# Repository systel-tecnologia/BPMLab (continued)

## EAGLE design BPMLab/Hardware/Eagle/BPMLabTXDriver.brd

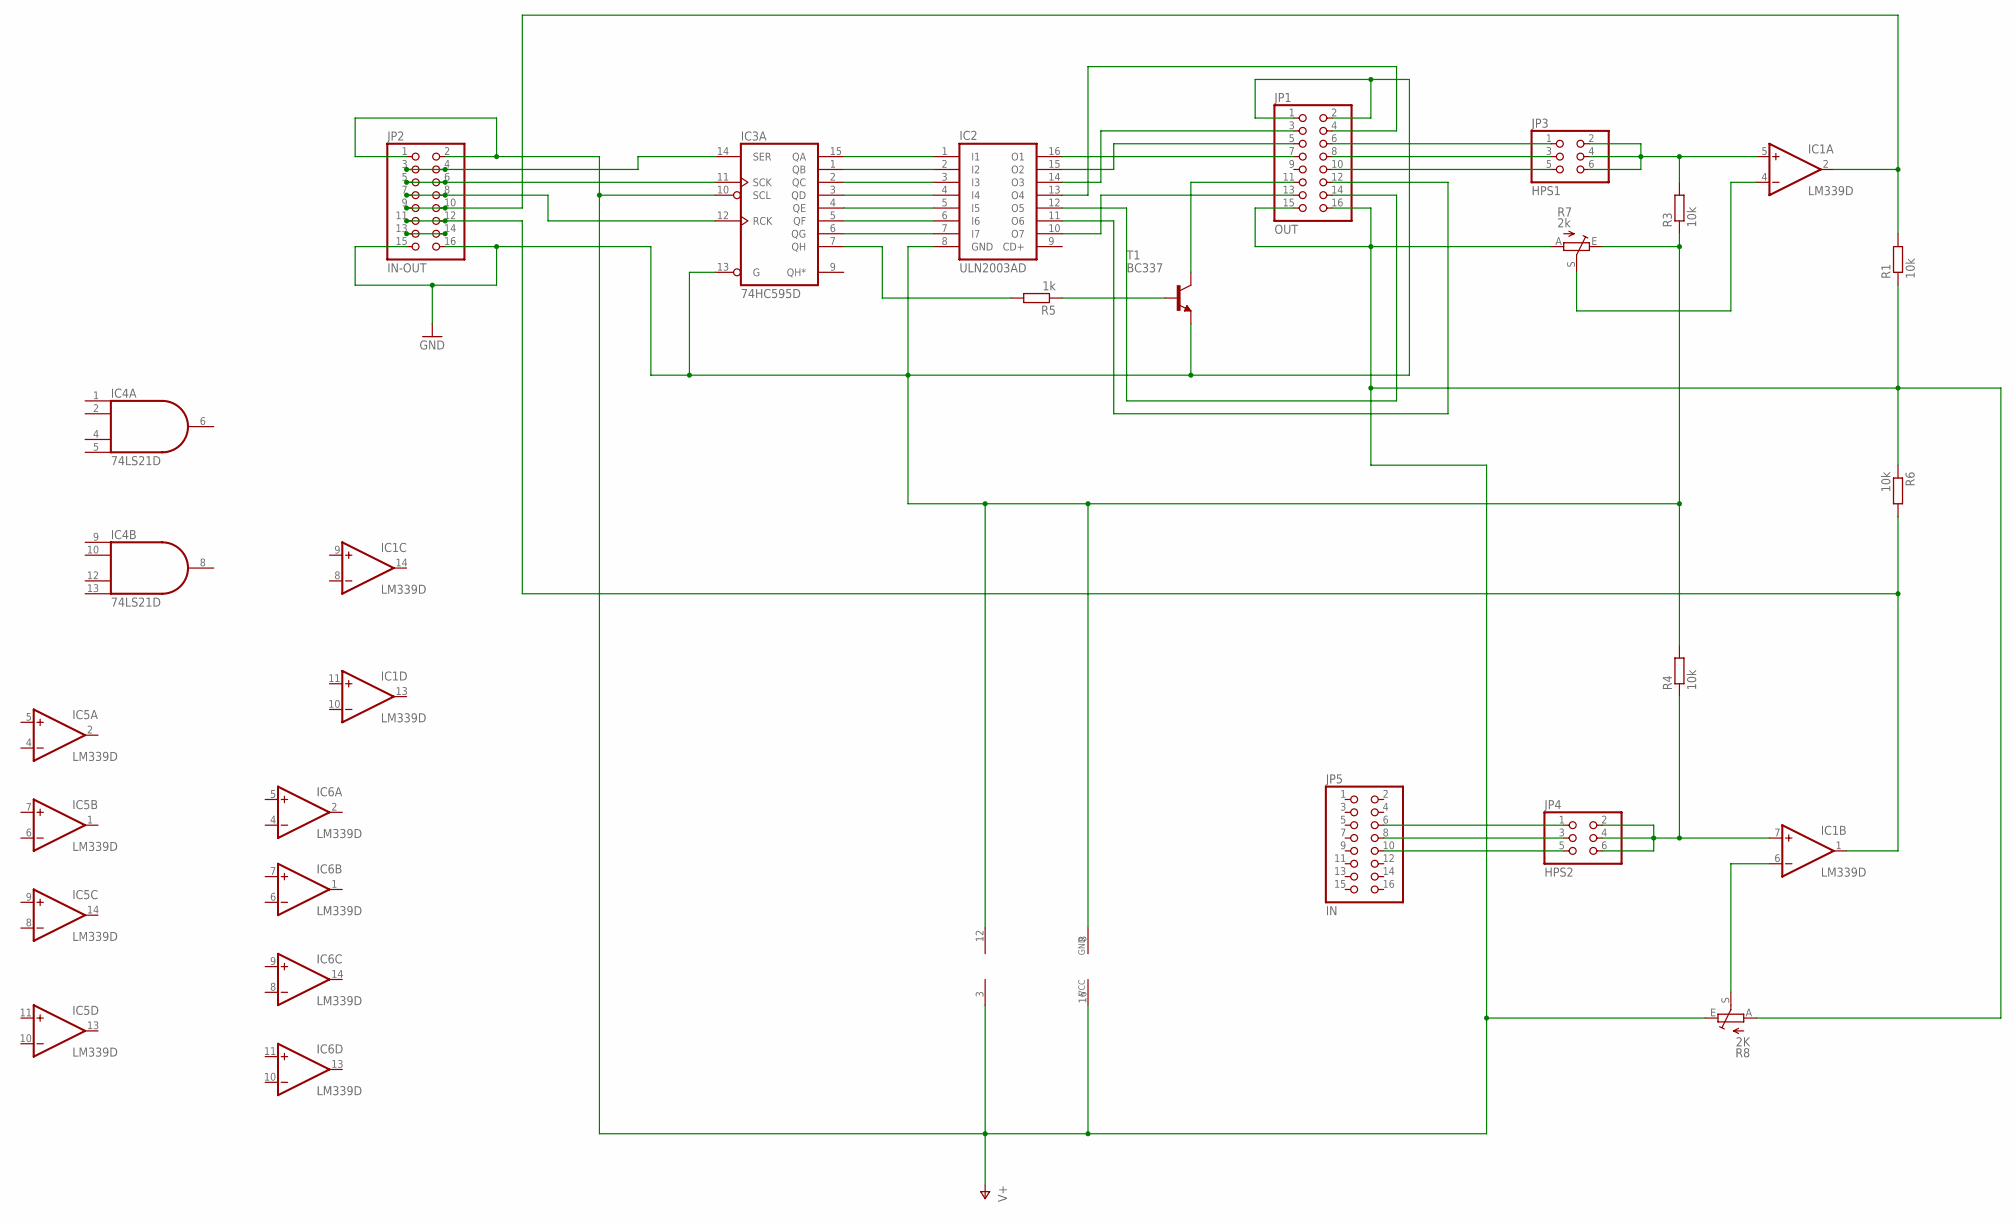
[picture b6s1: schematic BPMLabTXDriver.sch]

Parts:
IC1, IC5, IC6: LM339D; SO14
IC2: ULN2003AD; SO16
IC3: 74HC595D; SO16
IC4: 74LS21D; SO14
JP1: OUT; 2X08
JP2: IN-OUT; 2X08
JP3: HPS1; 2X03
JP4: HPS2; 2X03
JP5: IN; 2X08
R1, R3, R4, R6: 10k; 0207/10
R5: 1k; 0207/10
R7: 2k; RS3
R8: 2K; RS3
T1: BC337; TO92-CBE

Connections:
GND: IC1.12 (GND), IC2.8 (GND), IC3.8 (GND), IC3.13 (G), IC4.7 (GND), IC5.12 (GND), IC6.12 (GND), JP1.1, JP1.2, JP2.15, JP2.16, R3.1, R4.2, R7.E, T1.E
unnamed: JP1.6, JP3.1
unnamed: JP1.8, JP3.3
unnamed: JP1.10, JP3.5
unnamed: IC1.5 (+IN), JP3.2, JP3.4, JP3.6, R3.2
unnamed: R5.1, T1.B
unnamed: IC3.7 (QH), R5.2
unnamed: JP1.11, T1.C
unnamed: JP4.1, JP5.6
unnamed: JP4.3, JP5.8
unnamed: JP4.5, JP5.10
unnamed: IC1.7 (+IN), JP4.2, JP4.4, JP4.6, R4.1
unnamed: IC2.1 (I1), IC3.15 (QA)
unnamed: IC1.4 (-IN), R7.S
unnamed: IC1.6 (-IN), R8.S
unnamed: IC3.14 (SER), JP2.3, JP2.4
unnamed: IC2.2 (I2), IC3.1 (QB)
unnamed: IC2.3 (I3), IC3.2 (QC)
unnamed: IC2.4 (I4), IC3.3 (QD)
unnamed: IC2.5 (I5), IC3.4 (QE)
unnamed: IC2.6 (I6), IC3.5 (QF)
unnamed: IC2.7 (I7), IC3.6 (QG)
unnamed: IC3.11 (SCK), JP2.5, JP2.6
unnamed: IC3.12 (RCK), JP2.7, JP2.8
unnamed: IC2.16 (O1), JP1.7
unnamed: IC2.15 (O2), JP1.5
unnamed: IC2.14 (O3), JP1.3
unnamed: IC2.13 (O4), JP1.4
unnamed: IC2.12 (O5), JP1.14
unnamed: IC2.11 (O6), JP1.12
unnamed: IC2.10 (O7), JP1.13
unnamed: IC1.2 (OUT), JP2.9, JP2.10, R1.2
unnamed: IC1.1 (OUT), JP2.11, JP2.12, R6.2
unnamed: JP2.13, JP2.14
V+: IC1.3 (V+), IC3.10 (SCL), IC3.16 (VCC), IC4.14 (VCC), IC5.3 (V+), IC6.3 (V+), JP1.15, JP1.16, JP2.1, JP2.2, R1.1, R6.1, R7.A, R8.A, R8.E

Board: 2 copper layers, 19 parts (0 on the bottom side), 35 nets, no tracks yet.

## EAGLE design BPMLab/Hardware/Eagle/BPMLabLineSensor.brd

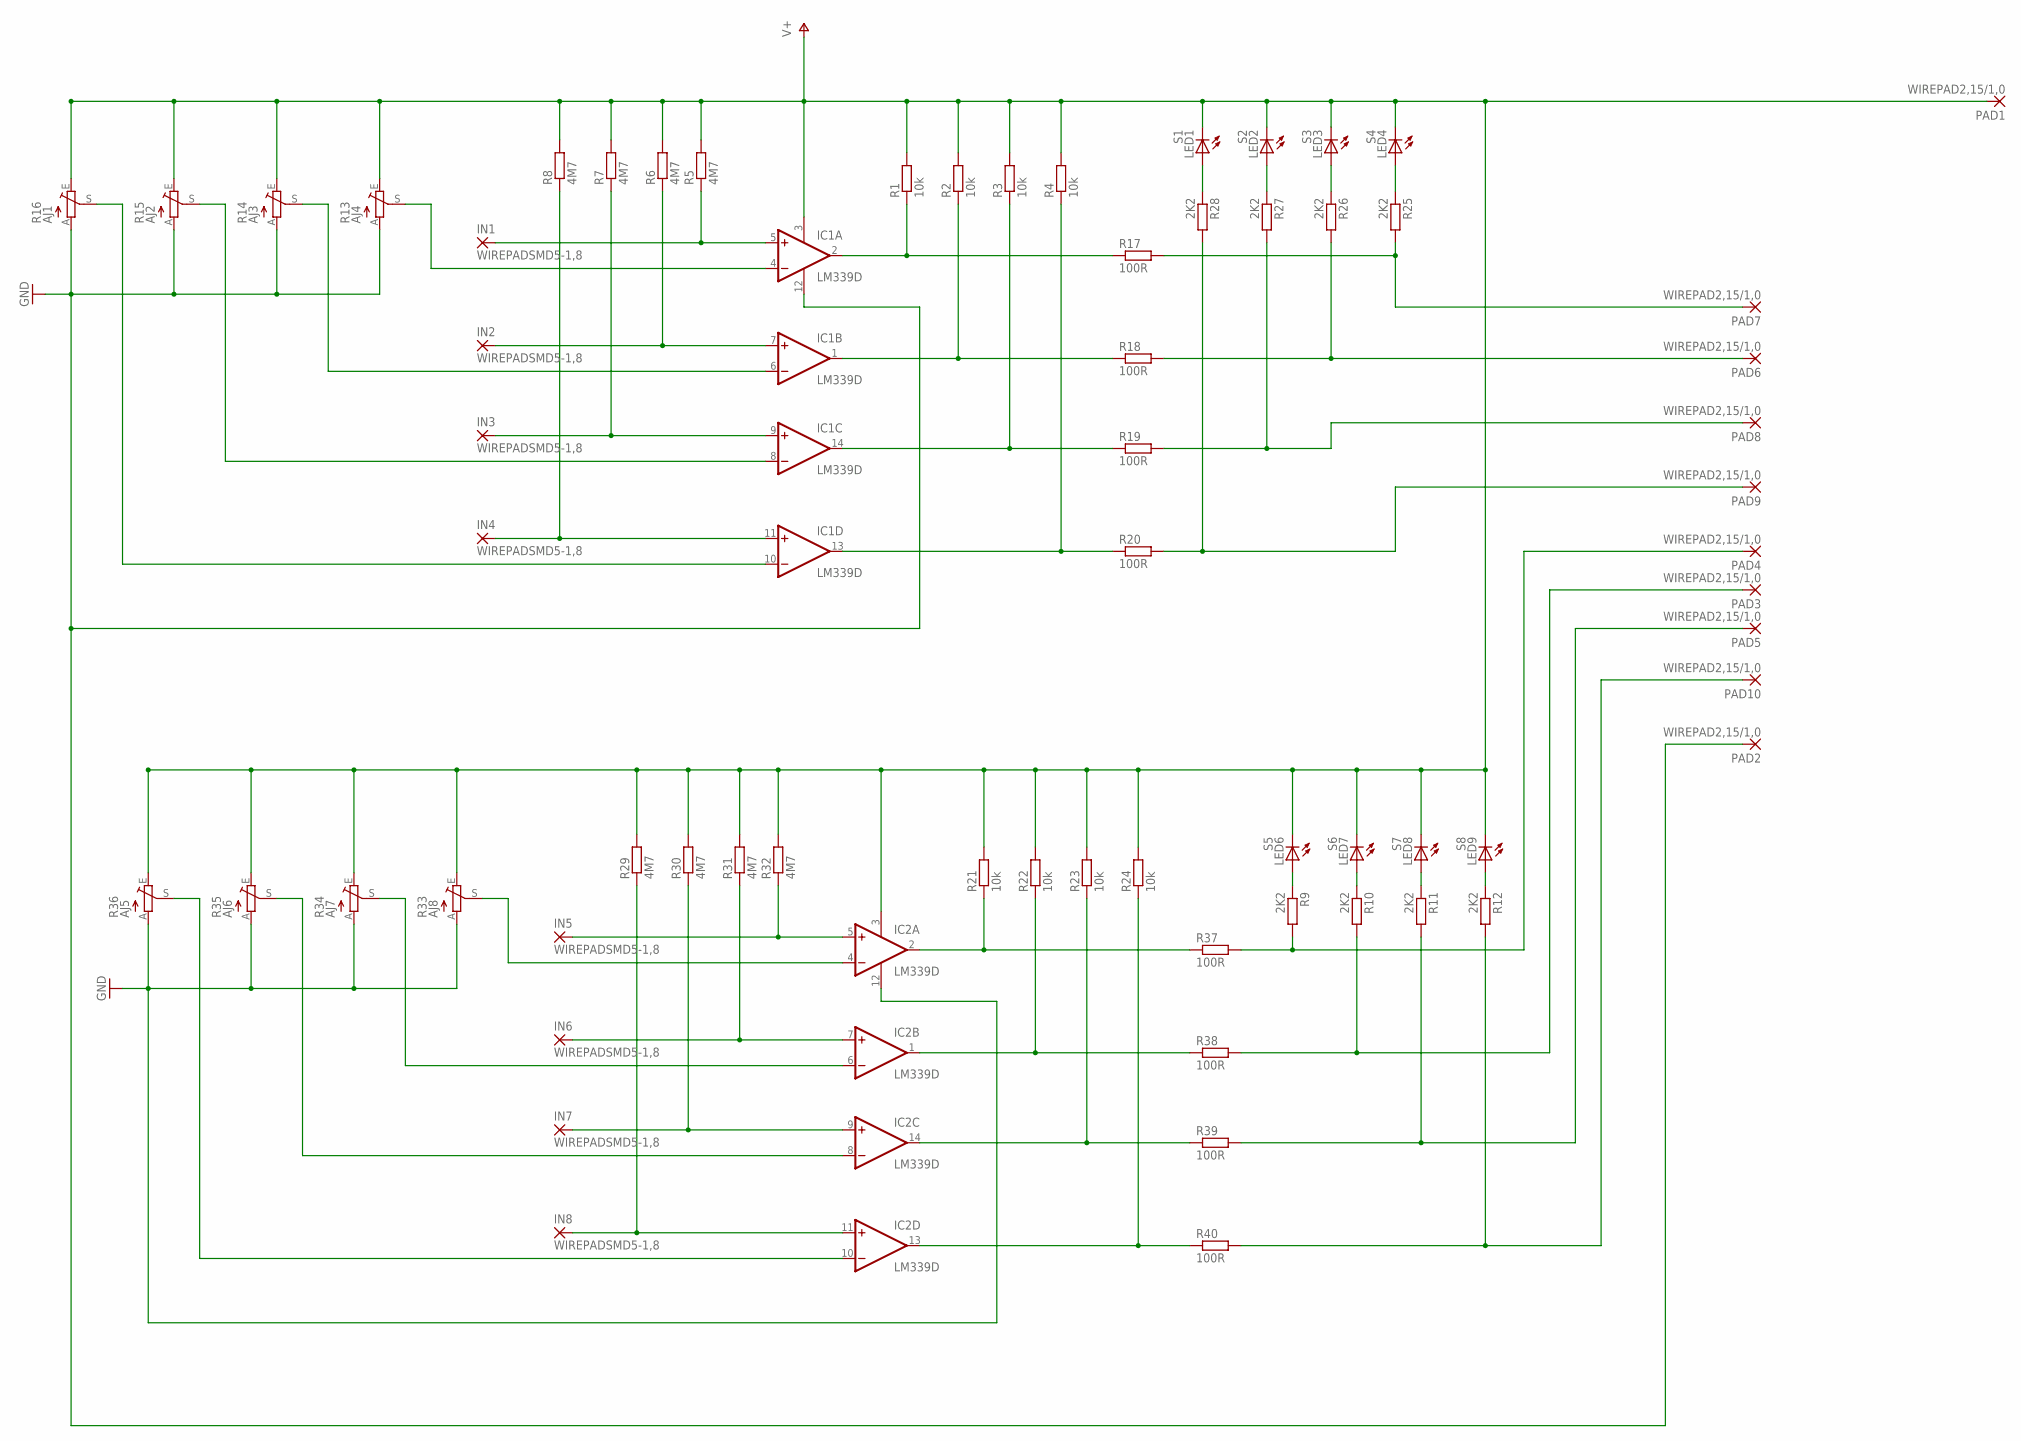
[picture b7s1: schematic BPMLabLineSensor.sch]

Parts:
IC1, IC2: LM339D; SO14
IN1, IN2, IN3, IN4, IN5, IN6, IN7, IN8: WIREPADSMD5-1,8; 5-1,8
LED1: S1; LED5MM
LED2: S2; LED5MM
LED3: S3; LED5MM
LED4: S4; LED5MM
LED6: S5; LED5MM
LED7: S6; LED5MM
LED8: S7; LED5MM
LED9: S8; LED5MM
PAD1, PAD2, PAD3, PAD4, PAD5, PAD6, PAD7, PAD8, PAD9, PAD10: WIREPAD2,15/1,0; 2,15/1,0
R1, R2, R3, R4, R21, R22, R23, R24: 10k; M0805
R5, R6, R7, R8, R29, R30, R31, R32: 4M7; M0805
R9, R10, R11, R12, R25, R26, R27, R28: 2K2; M0805
R13: AJ4; RS3
R14: AJ3; RS3
R15: AJ2; RS3
R16: AJ1; RS3
R17, R18, R19, R20, R37, R38, R39, R40: 100R; 0204/7
R33: AJ8; RS3
R34: AJ7; RS3
R35: AJ6; RS3
R36: AJ5; RS3

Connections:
GND: IC1.12 (GND), IC2.12 (GND), PAD2.1, R13.A, R14.A, R15.A, R16.A, R33.A, R34.A, R35.A, R36.A
unnamed: IC1.2 (OUT), R1.1, R17.1
unnamed: IC1.1 (OUT), R2.1, R18.1
unnamed: IC1.14 (OUT), R3.1, R19.1
unnamed: IC1.13 (OUT), R4.1, R20.1
unnamed: IC1.5 (+IN), IN1.1, R5.1
unnamed: IC1.7 (+IN), IN2.1, R6.1
unnamed: IC1.9 (+IN), IN3.1, R7.1
unnamed: IC1.11 (+IN), IN4.1, R8.1
unnamed: IC1.10 (-IN), R16.S
unnamed: IC1.8 (-IN), R15.S
unnamed: IC1.4 (-IN), R13.S
unnamed: IC1.6 (-IN), R14.S
unnamed: PAD3.1, R10.2, R38.2
unnamed: PAD4.1, R9.2, R37.2
unnamed: LED6.A, R9.1
unnamed: LED7.A, R10.1
unnamed: LED8.A, R11.1
unnamed: LED9.A, R12.1
unnamed: PAD7.1, R17.2, R25.2
unnamed: PAD9.1, R20.2, R28.2
unnamed: PAD8.1, R19.2, R27.2
unnamed: IC2.2 (OUT), R21.1, R37.1
unnamed: PAD6.1, R18.2, R26.2
unnamed: IC2.1 (OUT), R22.1, R38.1
unnamed: LED1.A, R28.1
unnamed: LED2.A, R27.1
unnamed: LED3.A, R26.1
unnamed: LED4.A, R25.1
unnamed: IC2.14 (OUT), R23.1, R39.1
unnamed: IC2.13 (OUT), R24.1, R40.1
unnamed: IC2.10 (-IN), R36.S
unnamed: IC2.8 (-IN), R35.S
unnamed: IC2.4 (-IN), R33.S
unnamed: IC2.6 (-IN), R34.S
unnamed: IC2.5 (+IN), IN5.1, R32.1
unnamed: IC2.7 (+IN), IN6.1, R31.1
unnamed: IC2.9 (+IN), IN7.1, R30.1
unnamed: IC2.11 (+IN), IN8.1, R29.1
unnamed: PAD10.1, R12.2, R40.2
unnamed: PAD5.1, R11.2, R39.2
V+: IC1.3 (V+), IC2.3 (V+), LED1.K (C), LED2.K (C), LED3.K (C), LED4.K (C), LED6.K (C), LED7.K (C), LED8.K (C), LED9.K (C), PAD1.1, R1.2, R2.2, R3.2, R4.2, R5.2, R6.2, R7.2, R8.2, R13.E, R14.E, R15.E, R16.E, R21.2, R22.2, R23.2, R24.2, R29.2, R30.2, R31.2, R32.2, R33.E, R34.E, R35.E, R36.E

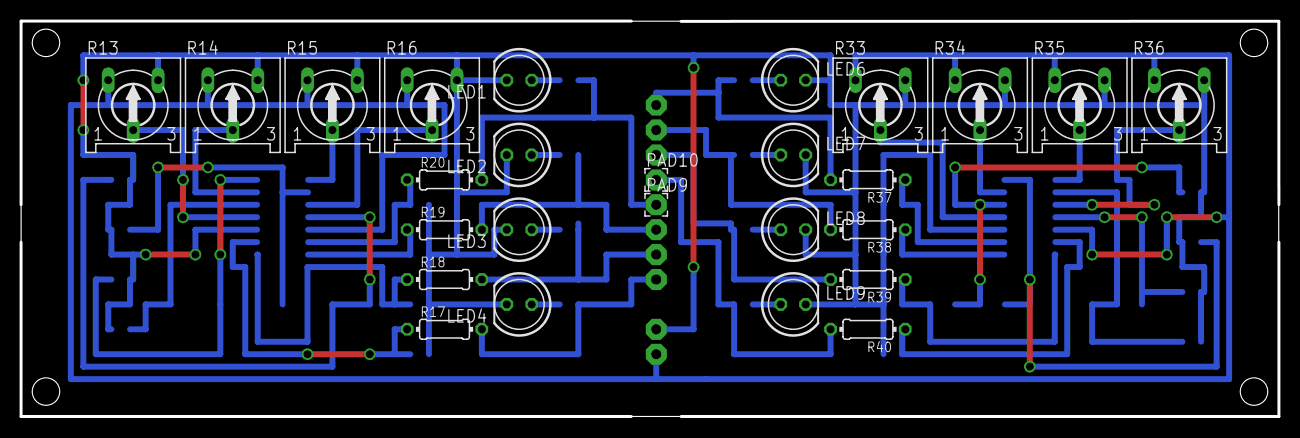
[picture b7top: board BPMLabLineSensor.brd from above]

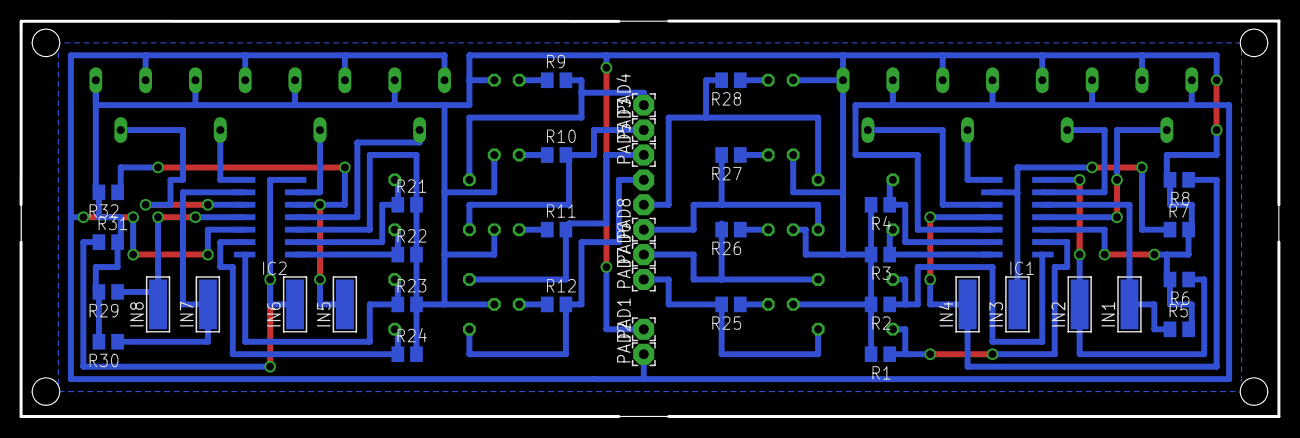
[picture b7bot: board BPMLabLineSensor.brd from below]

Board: 2 copper layers, 128.3 x 40.3 mm, 68 parts (42 on the bottom side), 42 nets.

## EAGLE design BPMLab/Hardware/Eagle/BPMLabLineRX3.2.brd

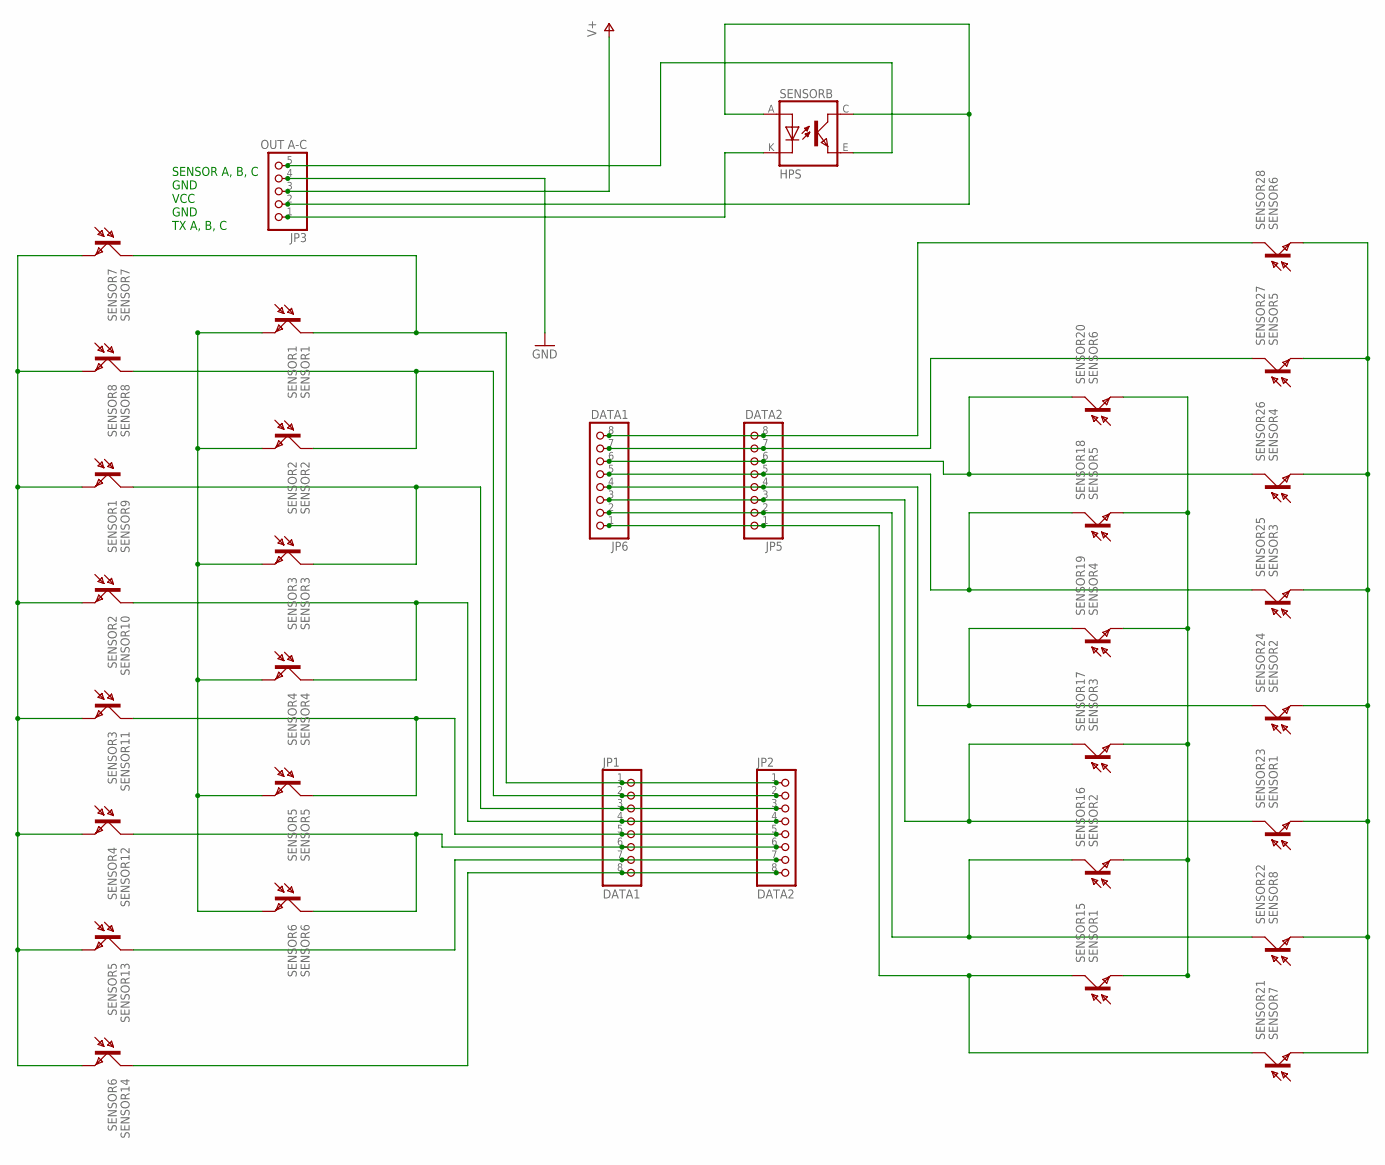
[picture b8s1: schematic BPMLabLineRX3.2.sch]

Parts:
JP1, JP6: DATA1; 1X08
JP2, JP5: DATA2; 1X08
JP3: OUT A-C; 1X05
SENSOR1, SENSOR9, SENSOR15, SENSOR23: SENSOR1; BPX81
SENSOR2, SENSOR10, SENSOR16, SENSOR24: SENSOR2; BPX81
SENSOR3, SENSOR11, SENSOR17, SENSOR25: SENSOR3; BPX81
SENSOR4, SENSOR12, SENSOR19, SENSOR26: SENSOR4; BPX81
SENSOR5, SENSOR13, SENSOR18, SENSOR27: SENSOR5; BPX81
SENSOR6, SENSOR14, SENSOR20, SENSOR28: SENSOR6; BPX81
SENSOR7, SENSOR21: SENSOR7; BPX81
SENSOR8, SENSOR22: SENSOR8; BPX81
SENSORB: HPS; TCRT5000

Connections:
GND: JP3.4
unnamed: JP5.1, JP6.1, SENSOR15.C, SENSOR21.C
unnamed: JP5.2, JP6.2, SENSOR16.C, SENSOR22.C
unnamed: JP1.1, JP2.1, SENSOR1.C, SENSOR7.C
unnamed: JP1.2, JP2.2, SENSOR2.C, SENSOR8.C
unnamed: SENSOR15.E, SENSOR16.E, SENSOR17.E, SENSOR18.E, SENSOR19.E, SENSOR20.E
unnamed: SENSOR21.E, SENSOR22.E, SENSOR23.E, SENSOR24.E, SENSOR25.E, SENSOR26.E, SENSOR27.E, SENSOR28.E
unnamed: JP5.3, JP6.3, SENSOR17.C, SENSOR23.C
unnamed: JP5.4, JP6.4, SENSOR19.C, SENSOR24.C
unnamed: JP3.5, SENSORB.E (EMITTER)
unnamed: JP3.1, SENSORB.K (CATHODE)
unnamed: SENSOR1.E, SENSOR2.E, SENSOR3.E, SENSOR4.E, SENSOR5.E, SENSOR6.E
unnamed: SENSOR7.E, SENSOR8.E, SENSOR9.E, SENSOR10.E, SENSOR11.E, SENSOR12.E, SENSOR13.E, SENSOR14.E
unnamed: JP1.3, JP2.3, SENSOR3.C, SENSOR9.C
unnamed: JP1.4, JP2.4, SENSOR4.C, SENSOR10.C
unnamed: JP1.5, JP2.5, SENSOR5.C, SENSOR11.C
unnamed: JP3.2, SENSORB.A (ANODE), SENSORB.C (COLLECTOR)
unnamed: JP1.6, JP2.6, SENSOR6.C, SENSOR12.C
unnamed: JP5.5, JP6.5, SENSOR18.C, SENSOR25.C
unnamed: JP1.7, JP2.7, SENSOR13.C
unnamed: JP1.8, JP2.8, SENSOR14.C
unnamed: JP5.6, JP6.6, SENSOR20.C, SENSOR26.C
unnamed: JP5.7, JP6.7, SENSOR27.C
unnamed: JP5.8, JP6.8, SENSOR28.C
V+: JP3.3

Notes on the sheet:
SENSOR A, B, C GND VCC GND TX A, B, C

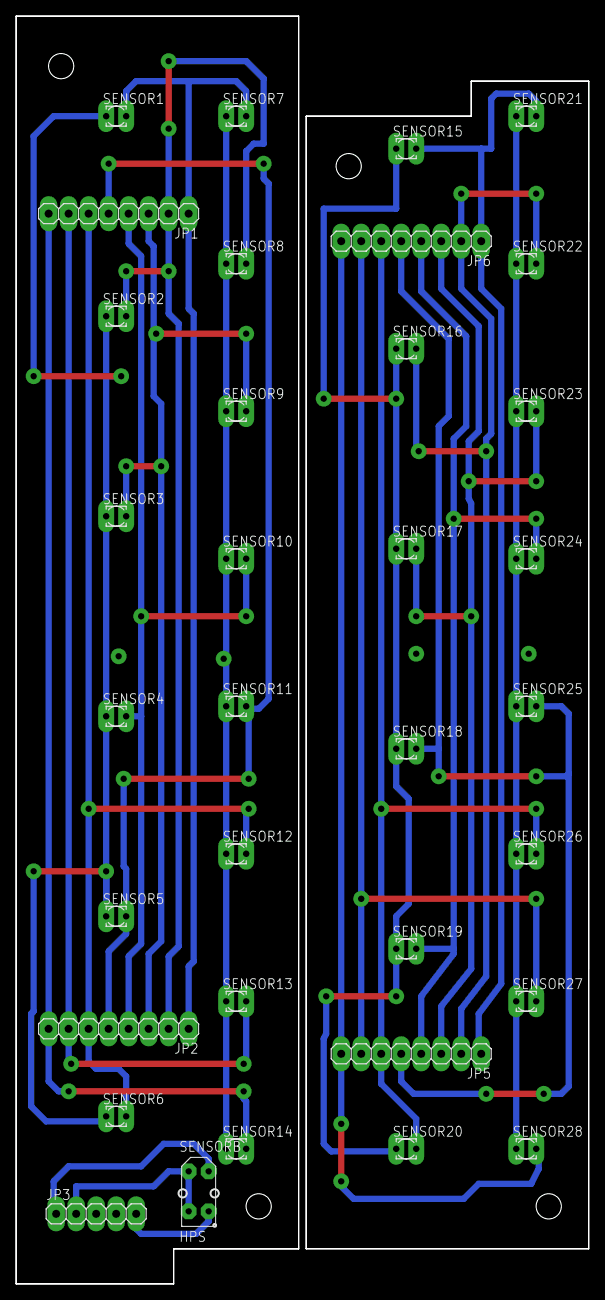
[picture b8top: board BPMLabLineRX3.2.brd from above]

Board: 2 copper layers, 72.7 x 161.0 mm, 34 parts (0 on the bottom side), 23 nets.

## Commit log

2019-03-21 Versão Inicial
2019-03-22 Correção de Status de Processo
2019-03-22 Tunning na tela de Processo para melhorar performance
2019-03-22 Gravação de configurações na EEPROM
2019-03-22 Tela de Conexão
2019-03-25 Integração com PC
2019-03-25 Remote Debug Connection
2019-03-25 PC Integration Application
2019-03-25 Hole Poke Implementation
2019-03-25 File Processor
2019-03-28 Integração de Nova placa de Transmissão
2019-04-01 Nova Sensorização
2019-04-01 Data e Hora dos Arquivos
2019-04-01 Compensação de Erro 1
2019-04-01 Inicio do Processador de Comandos
2019-04-02 Ajuste Final de Holepoke
2019-04-03 Ajuste Final
2019-04-04 Mais Implementação de Aplicativo
2019-04-11 Projeto de Hardware
2019-04-16 Adequação de Biblioteca Equino e Projeto de Hardware Proteus
2019-04-24 Controle Remoto
2019-04-25 Automação Remota Continuação 1
2019-04-26 Movimento de arena
2019-04-26 Analise de Arquivo
2019-04-27 Tela de Analise Parte Estatistica
2019-04-30 Estatisticas Parte 2 e Graficos Parte 3
2019-05-01 Calibragem Satisfatória
2019-05-05 Versão Final
2019-05-13 Integração de Console na Aplicação
2019-06-23 Primeira Correção de erro no Relógio
2019-06-23 Segunda Correção de erro no Relógio
2019-09-01 Nova Interface de Sensores
2019-09-03 Versão 2 Final
2019-09-04 Ultima Versão BPM
2019-09-22 Alteração de Frontend
2020-03-30 Mudanças ocorridas ao longo da produção
